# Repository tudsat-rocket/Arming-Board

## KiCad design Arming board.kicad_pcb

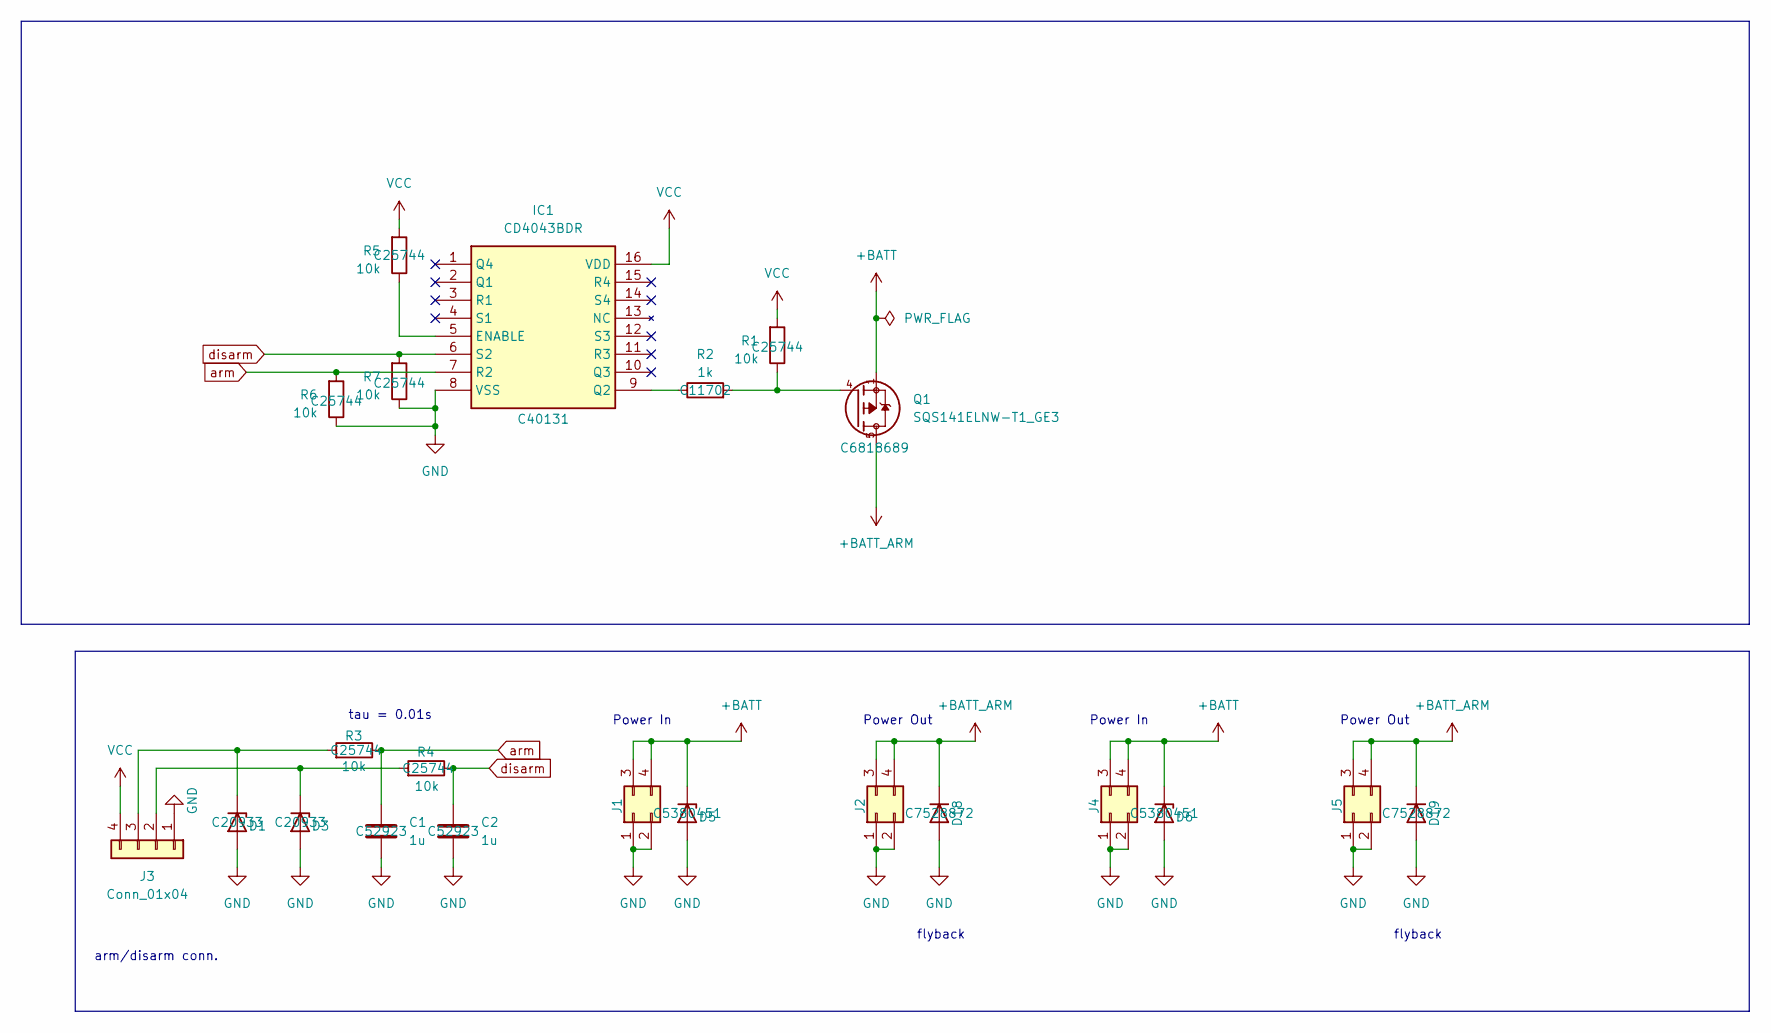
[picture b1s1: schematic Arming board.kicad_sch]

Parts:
C1, C2: 1u; C_0402_1005Metric; LCSC C52923
D1, D3: ESD5Zxx; D_SOD-523; LCSC C20933
D5, D6: TS1811LD-CX; D_SOD-523; LCSC C5380451
D18, D19: D; D_SOD-323_HandSoldering; LCSC# C7528872
IC1: CD4043BDR; SOIC-16W_7.5x10.3mm_P1.27mm; Mouser Part Number 595-CD4043BDR
J1, J2, J4, J5: Molex_Micro-Fit_3.0_43045-0400_2x02_P3.00mm_Horizontal; LCSC# x
J3: Conn_01x04; Molex_Micro-Fit_3.0_43650-0400_1x04_P3.00mm_Horizontal
Q1: SQS141ELNW-T1_GE3; PowerPAK_SO-8_Single; LCSC C6818689
R1, R3, R4, R5, R6, R7: 10k; R_0402_1005Metric_Pad0.72x0.64mm_HandSolder; LCSC C25744
R2: 1k; R_0402_1005Metric_Pad0.72x0.64mm_HandSolder; LCSC C11702

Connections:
+BATT: D5.1 (K), D6.1 (K), J1.3, J1.4, J4.3, J4.4, Q1.1, Q1.2, Q1.3
+BATT_ARM: D18.1 (K), D19.1 (K), J2.3, J2.4, J5.3, J5.4, Q1.5
GND: C1.2, C2.2, D1.2 (A), D3.2 (A), D5.2 (A), D6.2 (A), D18.2 (A), D19.2 (A), IC1.8 (VSS), J1.1, J1.2, J2.1, J2.2, J3.1, J4.1, J4.2, J5.1, J5.2, R6.1, R7.1
unnamed: D1.1 (K), J3.3, R3.2
unnamed: D3.1 (K), J3.2, R4.2
unnamed: IC1.5 (ENABLE), R5.1
unnamed: IC1.9 (Q2), R2.1
unnamed: Q1.4, R1.1, R2.2
VCC: IC1.16 (VDD), J3.4, R1.2, R5.2
arm: C1.1, IC1.7 (R2), R3.1, R6.2
disarm: C2.1, IC1.6 (S2), R4.1, R7.2

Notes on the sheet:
Power Out
flyback
Power In
arm/disarm conn.
tau = 0.01s

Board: 4 copper layers, 22 parts (0 on the bottom side), 11 nets, no tracks yet.

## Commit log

2026-05-01 continued scematic
2026-05-04 continued schematic
2026-05-07 finished first scematic draft
2026-05-18 Replaced 6-Pin with 4-Pin connector, added input pulldown
2026-05-18 Replaced connector with molex, fixed mosfet footprint
